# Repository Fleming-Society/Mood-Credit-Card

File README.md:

# Mood Credit Card

An educational electronics project from Fleming Society's 2024 Project X
programme. Participants use an ESP32-C3, a MAX30102 optical pulse sensor and
five LEDs to learn embedded programming, signal processing and PCB design.

> [!IMPORTANT]
> This is an educational demonstration, not a medical device. Heart-rate
> readings must not be used for diagnosis, monitoring or treatment.

## At a glance

| Item | Details |
| --- | --- |
| Programme | Project X 2024 |
| Topics | Arduino, ESP32-C3, sensors, I2C, signal processing and PCB design |
| Main hardware | ESP32-C3 SuperMini, MAX30102 module, five LEDs and five 220 Ω resistors |
| Firmware | Arduino sketch using the DevXplained MAX3010x Sensor Library |
| Design tools | KiCad, SolidWorks and a retained legacy DesignSpark PCB file |
| Current status | Recovered 2024 teaching pack; technical revalidation is required before another delivery |

## Project preview

| Project X workshop | Mood Credit Card model |
| --- | --- |
|  |  |

### Circuit schematic

## Start here

- **Learners:** begin with the [session materials](docs/learner/README.md),
  then open the [student firmware](firmware/student/mood_credit_card/).
- **Instructors:** read the [instructor notes](docs/instructor/README.md) and
  recovered session plans before preparing a session.
- **Hardware contributors:** read the [hardware guide](hardware/README.md)
  before editing or manufacturing the PCB.

PDF handouts survive for sessions 1, 3 and 5. Session 2 now has its recovered
agenda and I2C example code. Session 5 also has editable helper slides and an
instructor plan. No separate Session 4 handout was found in the source archive.

## Repository structure

```text
.
|-- docs/             # Learner and instructor material
|-- firmware/         # Maintained code, examples and historical snapshots
|-- hardware/         # Current CAD, enclosure source and historical revisions
|-- private/          # Local-only records and raw source archives, ignored by Git
|-- third_party/      # Imported material and preserved licence texts
|-- CONTRIBUTING.md
|-- LICENSE
`-- NOTICE.md
```

This layout is intended to be reused across Fleming Society projects:
documentation in `docs/`, runnable code in `firmware/`, editable engineering
source in `hardware/`, and personal or operational records outside the public
Git history.

## Recovered 2024 material

| Material | Location | Notes |
| --- | --- | --- |
| Learner handouts, PCB guide and I2C slides | [`docs/learner/2024/`](docs/learner/2024/) | Original 2024 files; review before reuse |
| Instructor agendas and plans | [`docs/instructor/2024/`](docs/instructor/2024/) | Session 2 and Session 5 material recovered |
| I2C Arduino examples | [`firmware/examples/session-02/`](firmware/examples/session-02/) | Arduino Uno slave and ESP8266 master |
| Learner KiCad project | [`hardware/kicad/learner/`](hardware/kicad/learner/) | Complete source set recovered; not yet revalidated |
| Enclosure CAD | [`hardware/enclosure/`](hardware/enclosure/) | SolidWorks source and STL exports |
| Historical PCB revisions | [`hardware/archive/2024/`](hardware/archive/2024/) | Seven labelled development stages; caches and automatic backups omitted |

## Software setup

1. Install the Arduino IDE and ESP32 board support.
2. Install the
   [MAX3010x Sensor Library](https://github.com/devxplained/MAX3010x-Sensor-Library)
   by DevXplained.
3. Open
   `firmware/student/mood_credit_card/mood_credit_card.ino`.
4. Select the correct ESP32-C3 board and port.
5. Compile before connecting the workshop PCB.

The exact Arduino ESP32 core and library versions used in 2024 were not
recorded. Pin these versions after the firmware is revalidated.

## Validation status

| Area | Status | Required action |
| --- | --- | --- |
| Learner materials | Recovered from 2024 | Review wording, links and software screenshots |
| Student firmware | Not recently compiled | Confirm board target, library version and sampling behaviour |
| Learner KiCad project | Source set recovered | Open in the intended KiCad version; run ERC and DRC |
| Exemplar KiCad design | Source preserved | Compare with an approved fabricated board |
| Enclosure CAD | Source and STL variants recovered | Confirm assembly references, fit and preferred revision |
| Component 3D models | Withheld pending licence review | Replace with redistributable models and document provenance |
| Gerbers | Current and historical sets preserved | Identify the approved set before manufacturing |
| Bill of materials | 2024 workbook preserved | Review prices, part numbers and substitutions |
| Risk assessment | Missing | Add the current session risk assessment and supervision notes |

## Safety

- Power the board only from the documented low-voltage USB supply.
- Inspect assembled boards for shorts before connecting them to a computer.
- Do not look directly into the pulse sensor LEDs at close range.
- Follow the venue's soldering, ESD and tool-safety procedures.
- Do not collect or publish participants' health readings or attendance data.

## Contributing

See [CONTRIBUTING.md](CONTRIBUTING.md) for file-placement, privacy and review
rules.

## Licensing

Except where a file or notice says otherwise, the original teaching material,
firmware and hardware designs are available under the [MIT License](LICENSE).

Third-party material retains its original copyright and licence. See
[NOTICE.md](NOTICE.md) and the licence texts under [`third_party/`](third_party/).

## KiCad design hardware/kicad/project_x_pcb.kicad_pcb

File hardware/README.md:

# Hardware

## Editable PCB sources

[`kicad/`](kicad/) contains the completed KiCad exemplar, custom symbols and
custom footprints. [`kicad/learner/`](kicad/learner/) contains the recovered
2024 learner starter project with its board, schematic and project file.

The board files use `${KIPRJMOD}`-relative references. The supplied component
STEP models are withheld from the public tree until their redistribution
rights are confirmed; see
[`kicad/3d_models/README.md`](kicad/3d_models/README.md).

## Enclosure CAD

[`enclosure/`](enclosure/) contains recovered SolidWorks source and STL
exports for the enclosure. Several back variants survive, and no preferred
release has been confirmed.

## Historical revisions

[`archive/2024/`](archive/2024/) contains seven labelled PCB development
stages recovered from the source ZIP. They are retained for traceability, not
as alternatives to the current exemplar or learner project.

## Manufacturing outputs

[`manufacturing/gerbers/`](manufacturing/gerbers/) contains the previously
selected historical Gerber and drill files. Additional revision-specific sets
are retained with their matching source under `archive/2024/`.

Do not send any set to manufacture until the schematic and PCB pass ERC, DRC
and a human design review against an approved fabricated board.

## Bill of materials

[`bom/2024/bom.xlsx`](bom/2024/bom.xlsx) is the supplied 2024 bill of
materials. Prices, stock, supplier links and part substitutions have not yet
been reviewed for a future delivery.

## Legacy source

[`legacy/`](legacy/) contains an older binary `.dip` design file. Retain it for
traceability until its application, version and relationship to the KiCad
design are documented.

## Repository hygiene

KiCad caches, user preferences and automatic backups are not public project
source. The untouched `project_x.zip` source drop is retained under ignored
`private/source-archive/` as a lossless fallback. Unverified third-party
models and libraries are held separately under `private/licensing-review/`
and are not covered by the project licence.

Before the next release:

- convert the BOM into a supplier-neutral master list with optional supplier
  columns;
- confirm board dimensions and connector pinout;
- choose and validate an enclosure revision;
- add assembly instructions and known design limitations; and
- record the KiCad version used for final ERC and DRC.

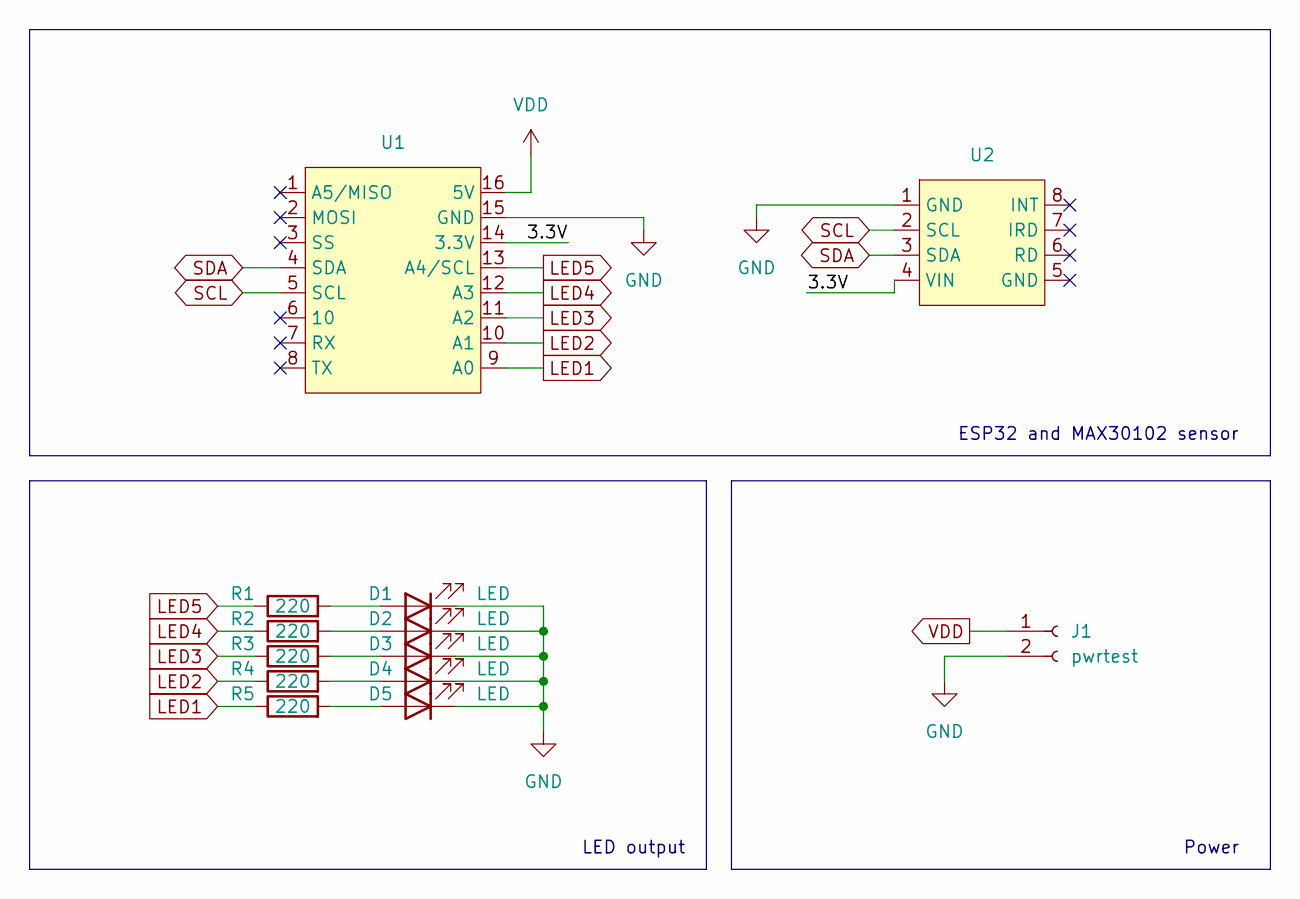
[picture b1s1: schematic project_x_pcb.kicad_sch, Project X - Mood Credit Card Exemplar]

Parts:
D1, D2, D3, D4, D5: LED; LED_0805_2012Metric_Pad1.15x1.40mm_HandSolder
J1: pwrtest; PinHeader_1x02_P2.54mm_Vertical
R1, R2, R3, R4, R5: 220; R_0805_2012Metric_Pad1.20x1.40mm_HandSolder
U1: esp32_super_mini
U2: MAX30102

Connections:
/3.3V: U1.14 (3.3V), U2.4 (VIN)
GND: D1.1 (K), D2.1 (K), D3.1 (K), D4.1 (K), D5.1 (K), J1.2, U1.15 (GND), U2.1 (GND)
LED1: R5.1, U1.9 (A0)
LED2: R4.1, U1.10 (A1)
LED3: R3.1, U1.11 (A2)
LED4: R2.1, U1.12 (A3)
LED5: R1.1, U1.13 (A4/SCL)
unnamed: D1.2 (A), R1.2
unnamed: D2.2 (A), R2.2
unnamed: D3.2 (A), R3.2
unnamed: D4.2 (A), R4.2
unnamed: D5.2 (A), R5.2
SCL: U1.5 (SCL), U2.2 (SCL)
SDA: U1.4 (SDA), U2.3 (SDA)
VDD: J1.1, U1.16 (5V)

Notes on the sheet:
Power
ESP32 and MAX30102 sensor
LED output

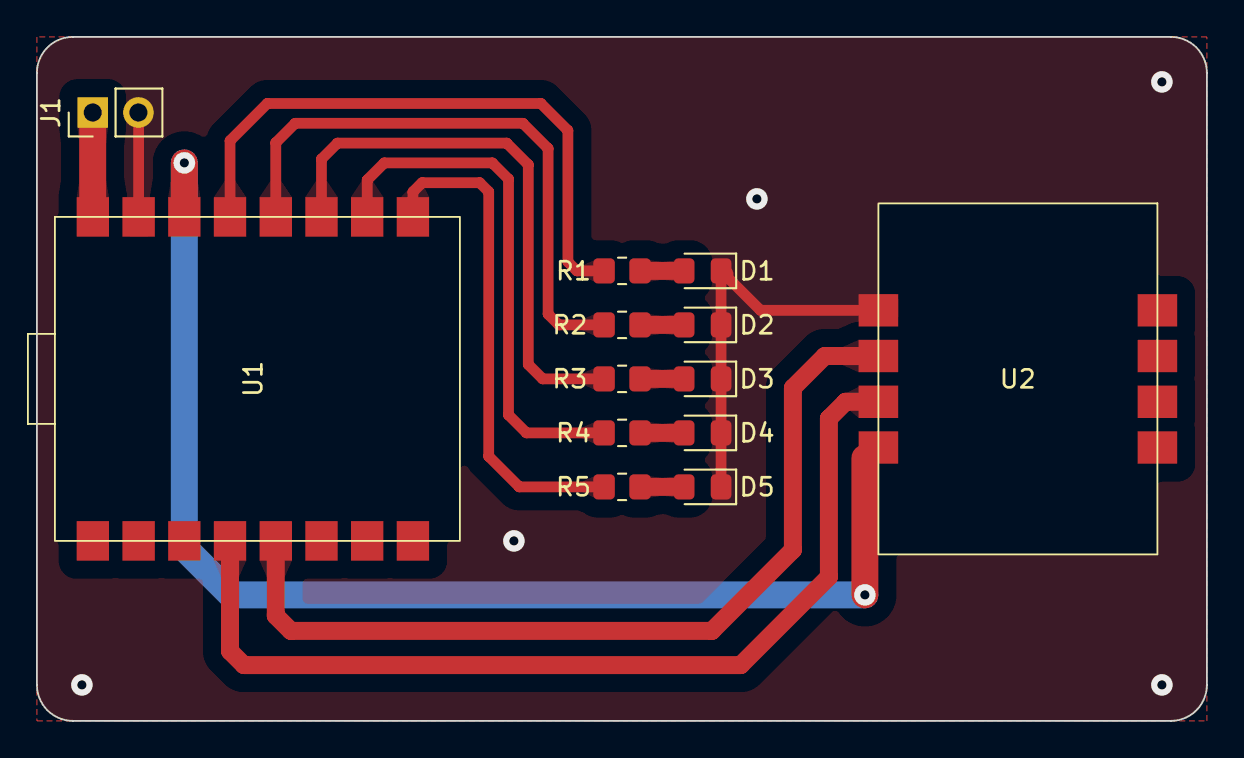
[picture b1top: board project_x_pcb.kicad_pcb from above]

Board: 2 copper layers, 65.0 x 38.0 mm, 13 parts (0 on the bottom side), 15 nets.

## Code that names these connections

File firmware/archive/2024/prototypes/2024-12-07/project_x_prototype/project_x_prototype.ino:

//----------------------------------CONFIGURATION, DO NOT CHANGE----------------------------------//
#include <MAX3010x.h>
#include "filters.h"

// Sensor (adjust to your sensor type)
MAX30105 sensor;
const auto kSamplingRate = sensor.SAMPLING_RATE_3200SPS;
const float kSamplingFrequency = 400.0;

// Finger Detection Threshold and Cooldown
const unsigned long kFingerThreshold = 10000;
const unsigned int kFingerCooldownMs = 500;

// Edge Detection Threshold (decrease for MAX30100)
const float kEdgeThreshold = -2000.0;

// Filters
const float kLowPassCutoff = 5.0;
const float kHighPassCutoff = 0.5;

// Timestamp of the last heartbeat
long last_heartbeat = 0;

// Timestamp for finger detection
long finger_timestamp = 0;
bool finger_detected = false;

// Last diff to detect zero crossing
float last_diff = NAN;
bool crossed = false;
long crossed_time = 0;

//------------------------------------------------------------------------------------------------//

//----- Averaging Parameters -----//
const bool kEnableAveraging = true;
const int kAveragingSamples = 5;
const int kSampleThreshold = 5;

// Filter Instances
HighPassFilter high_pass_filter(kHighPassCutoff, kSamplingFrequency);
LowPassFilter low_pass_filter(kLowPassCutoff, kSamplingFrequency);
Differentiator differentiator(kSamplingFrequency);
MovingAverageFilter<kAveragingSamples> averager;

//----- Define your LEDs here -----//
#define LED1 A0
#define LED2 A1
#define LED3 A2
#define LED4 A3
#define LED5 A4

//----- Define your variables here -----//

// BPM as global var
int bpm;
int bpm_out;

int led1state, led2state, led3state, led4state, led5state = 0;
long currentMillis, prevMillis = 0;


//----- Setup Function (runs once) -----//
void setup() {


  Serial.begin(115200);  //baud rate
  delay(100);
  Serial.println("Serial start");
  delay(100);
  Serial.println("LED test");
  analogWrite(LED1, 255);
  analogWrite(LED2, 255);
  analogWrite(LED3, 255);
  analogWrite(LED4, 255);
  analogWrite(LED5, 255);
  delay(1000);
  analogWrite(LED1, 0);
  analogWrite(LED2, 0);
  analogWrite(LED3, 0);
  analogWrite(LED4, 0);
  analogWrite(LED5, 0);

  //Sensor initialisation
  if (sensor.begin() && sensor.setSamplingRate(kSamplingRate)) {
    Serial.println("Sensor initialized");
  } else {
    Serial.println("Sensor not found");
    while (1)
      ;
  }
}

//----- Main Function (repeats forever) -----//
void loop() {

  bpm = readBPM();
  // delay(50);
  currentMillis = millis();
  if (currentMillis - prevMillis > 1000) {
    if (bpm == -1) {
      Serial.println("No BPM detected.");
    } else {
      Serial.println(bpm);
    }
    Serial.print(">>> The function output is:");
    Serial.println(bpm);
    prevMillis = currentMillis;
  }

  //----- Define your LEDs here -----//
  int val = 10;

  if (bpm > 150) {
    led1state = val;
    led2state = val;
    led3state = val;
    led4state = val;
    led5state = val;
  } else if (bpm >= 95) {
    led1state = val;
    led2state = val;
    led3state = val;
    led4state = val;
    led5state = 0;
  } else if (bpm >= 85) {
    led1state = val;
    led2state = val;
    led3state = val;
    led4state = 0;
    led5state = 0;
  } else if (bpm >= 80) {
    led1state = val;
    led2state = val;
    led3state = 0;
    led4state = 0;
    led5state = 0;
  } else if (bpm >= 50) {
    led1state = val;
    led2state = 0;
    led3state = 0;
    led4state = 0;
    led5state = 0;
  } else {
    led1state = 0;
    led2state = 0;
    led3state = 0;
    led4state = 0;
    led5state = 0;
  }
  analogWrite(LED1, led1state);
  analogWrite(LED2, led2state);
  analogWrite(LED3, led3state);
  analogWrite(LED4, led4state);
  analogWrite(LED5, led5state);
}

int readBPM() {
  auto sample = sensor.readSample(1000);  // Read sensor data
  float current_value = sample.red;

  // Finger detection using raw sensor value
  if (current_value > kFingerThreshold) {
    if (millis() - finger_timestamp > kFingerCooldownMs) {
      finger_detected = true;
    }
  } else {
    // Reset filters and variables when the finger is removed
    differentiator.reset();
    averager.reset();
    low_pass_filter.reset();
    high_pass_filter.reset();
    finger_detected = false;
    finger_timestamp = millis();
    return -1;  // Return -1 if no finger is detected
  }

  if (finger_detected) {
    // Process signal with filters
    current_value = low_pass_filter.process(current_value);
    current_value = high_pass_filter.process(current_value);
    float current_diff = differentiator.process(current_value);

    if (!isnan(current_diff) && !isnan(last_diff)) {
      // Detect zero-crossing (heartbeat event)
      if (last_diff > 0 && current_diff < 0) {
        crossed = true;
        crossed_time = millis();
      }

      if (current_diff > 0) {
        crossed = false;
      }

      // Detect falling edge of the waveform
      if (crossed && current_diff < kEdgeThreshold) {
        if (last_heartbeat != 0 && crossed_time - last_heartbeat > 300) {
          // Calculate BPM
          int raw_bpm = 60000 / (crossed_time - last_heartbeat);
          bpm_out = raw_bpm;
          // // Debug
          // Serial.print("BPM raw:");
          // Serial.println(raw_bpm);

          // Apply averaging if enabled
          if (kEnableAveraging) {
            int avg_bpm = averager.process(raw_bpm);

            // Update bpm_out only if enough samples have been averaged
            if (averager.count() > kSampleThreshold) {
              bpm_out = avg_bpm;
              // Debug
              Serial.print("BPM avg:");
              Serial.println(raw_bpm);
            }
          }
        }

        // Reset for next detection
        crossed = false;
        last_heartbeat = crossed_time;
      }
    }

    last_diff = current_diff;
  }

  // Return bpm_out (default is 0 if no heartbeat detected yet)
  return bpm_out;  // Return -1 if BPM is invalid
  // delay(1000);
}

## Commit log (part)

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2024-11-13 Session 1
2024-12-16 Update Project X Files
    Added session scripts and exemplar PCB files.
